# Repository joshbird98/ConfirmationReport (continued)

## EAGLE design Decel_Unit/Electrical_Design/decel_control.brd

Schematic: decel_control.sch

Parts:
ADC_FAST_HV1_FB: MCP33131; MSOP10
ADC_HV1_ELECTRODE_CURRENT, ADC_HV1_FG: MCP33131; MSOP10
ADC_SLOW_HV1_FB: MAX11270; TSSOP24
ADC_TEMP_DAC_HV1_CTRL: MCP33131; MSOP10
BNC_DECEL_COPY: BNC_RS
C1, C2, C4, C9, C10, C11, C13, C15, C16, C17, C18, C23, C24, C28, C34, C35, C36, C38, C45, C55, C56, C58, C59, C60, C64, C68, C74, C76, C79, C84, C89, C90, C91, C92, C103, C104, C109, C122, C132, C135, C136: 100n; C0805
C3, C5, C51: 10u; SMC_B
C6, C7, C8, C19, C20, C21, C30, C31, C32, C61, C62, C63, C66, C70, C110, C129, C130: 10u; C/6032-28R
C12, C14, C37, C54, C65, C77, C98, C133, C137: 1n; C0805
C22, C67, C72, C73, C80, C83, C93, C94, C95, C96, C97, C124, C126: 10n; C0805
C25, C57, C69, C75, C99, C105, C106, C113, C115, C125, C127, C131, C134: 1u; C0805
C26, C71, C78, C123: 1.7n; C0805
C27, C33, C40, C46, C47, C53: 0.1uF; 0402-TIGHT
C29, C43: 2.2uF; 0402-TIGHT
C39, C41: 15pF; 0402-TIGHT
C42, C52, C82, C85, C86, C87, C88: 100u; D/7343-31W
C44, C50: 22pF; 0402-TIGHT
C48: 1.0uF; 0402-TIGHT
C49: 4.7uF; 0402-TIGHT
C81: 2n; C0805
C100, C101: 100n; C0603
C102, C118: 10u; C0603
C107, C108, C117, C121: 22u; C0603
C111, C112: 1n; C0603
C114, C120: 2u2; C0603
C116, C128: 10n_C0G; C0805
C119: 10n; C0603
CLIP1, CLIP2, CLIP3, CLIP4: RFI_SHIELD_CLIP
CONN1: PSU_CONNECTOR; PSU_CONNECTION
D1, D2, D3, D4, D5, D6: BAS40-04; SOT23
DAC_HV1_CTRL: AD5763; TQFP-32
DAC_ULTRAVOLT_CTRL: AD5763; TQFP-32
EXT_INTERLOCK: KK-156-2
FRONT_PANEL_INTERLOCK: KK-156-2
F_RX1: HFBR-2412-TZ; HFBR-X41XZ
F_TX1: HFBR-1412-TZ; HFBR-X41XZ
HV_ENABLED_LED: LEDCHIPLED_0805; CHIPLED_0805
HV_PSU1, HV_PSU2: ULTRAVOLT_20A
IC1, IC2, IC3, IC4, IC5, IC6, IC9, IC10: ADA4522-4; SO14
IC7, IC8: AD8034; SOIC8
IP_BNC_HV1_FB, IP_BNC_HV1_PSU_EXTERNAL_OFFSET: BNC_RS
J1: MTA04-156; 1X4MTA
JP1: PINHD-1X8-3.5MM; 1X08-3.5MM
K1, K3: FINDER-30.22
K2: AQY41SOP; SOP04
LED1, LED2, LED3: LEDCHIP-LED0805; CHIP-LED0805
LID1_INTERLOCK, LID2_INTERLOCK: KK-156-2
MUX1: TMUX1104; VSSOP-10
OP_BNC_HV1_FG_COPY: BNC_RS
Q1: MOSFET-NREFLOW; SOT23
R1, R27, R28, R51, R54, R55, R61, R69, R108, R109, R110, R111, R112: 1k; R0805
R2: 88; R0805
R3, R102: 560; R0805
R4, R5, R6, R11, R12, R21, R22, R23, R25, R39, R41, R43, R49, R50, R56, R57, R58, R60, R63, R64, R65, R67, R68, R70, R71, R73, R78, R85, R86, R87, R91: 1000; R0805
R7, R10, R24, R31, R32, R34, R35, R36, R37, R52, R93, R98, R105, R107: 10k; R0805
R8, R62, R100: 100; R0805
R9: 200; R0805
R13, R18: 11k; R0805
R14, R15, R16, R17, R19, R20: 18k; R0805
R26, R53, R59, R106: 22; R0805
R29, R30: 22; 0402-TIGHT
R33, R38, R44, R46, R81, R82, R83, R84: 10; R0805
R40: 7500; R0805
R42: 5.1k; 0402-TIGHT
R45: 20000; R0805
R47: 15000; R0805
R48: 68000; R0805
R66: dnf; R0805
R72: 390; R0805
R74: 20k; R0805
R75: 330; R0805
R76, R116: 100k; R0805
R77: 270; R0805
R79: 1800; R0805
R80: 430; R0805
R88, R89: 1300; R0805
R90, R92: 150.0; R0805
R94, R96, R97, R99, R101, R103, R104: 7k32; R0603
R95: 5k11; R0603
R113: 82k; R0805
R114: 1000k; R0805
R115: 22k; R0805
TC1: MAX31855; SOIC8
TMP1, TMP2: MCP9700; SC70-5L
TP_REF, TP_REF1: TPB1,27; B1,27
TRIM1, TRIM2: 20; BOURNS_TRIMPOT
TRIM3: 10k; BOURNS_TRIMPOT
U1: STM32F405RGT6; TQFP64
U$1: SN75451; SOIC8
U$2: POWER_BOARD_DECEL
VREF1: MAX6225ACSA+; SOIC8
VREG1: LT3085; MSOP8
X1: PN61729-S
X2: 22-23-2021
X3: 2510-; PAK100/2500-10
X4: W237-102
Y1: 32.768kHz; CRYSTAL-SMD-3.2X1.5MM
Y2: 12MHz; CRYSTAL-SMD-5X3.2-4PAD

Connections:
0: ADC_FAST_HV1_FB.4 (AIN-), ADC_FAST_HV1_FB.5 (GND), ADC_HV1_ELECTRODE_CURRENT.4 (AIN-), ADC_HV1_ELECTRODE_CURRENT.5 (GND), ADC_HV1_FG.4 (AIN-), ADC_HV1_FG.5 (GND), ADC_SLOW_HV1_FB.10 (AVSS), ADC_SLOW_HV1_FB.11 (AINN), ADC_SLOW_HV1_FB.13 (REFN), ADC_SLOW_HV1_FB.17 (AVSS2), ADC_TEMP_DAC_HV1_CTRL.4 (AIN-), ADC_TEMP_DAC_HV1_CTRL.5 (GND), BNC_DECEL_COPY.P$1 (S4), BNC_DECEL_COPY.P$2 (S3), BNC_DECEL_COPY.P$3 (S2), BNC_DECEL_COPY.P$4 (S1), C6.+, C7.-, C9.2, C11.2, C12.2, C13.1, C14.1, C15.2, C16.2, C17.2, C18.2, C19.+, C20.-, C21.-, C22.2, C24.2, C25.2, C26.2, C28.2, C30.+, C31.-, C34.2, C35.2, C37.2, C38.2, C54.1, C55.1, C57.2, C58.2, C59.2, C60.2, C61.-, C62.-, C63.+, C64.1, C65.1, C66.-, C67.2, C69.2, C70.-, C71.2, C72.2, C73.1, C75.2, C76.2, C77.2, C78.2, C79.2, C80.2, C81.2, C83.1, C85.-, C86.-, C87.-, C90.2, C91.2, C92.2, C93.2, C94.2, C95.2, C96.2, C97.2, C98.2, C99.2, C100.2, C101.2, C102.1, C103.2, C104.2, C105.2, C106.2, C109.2, C110.-, C111.2, C112.2, C113.2, C114.2, C115.2, C116.1, C118.2, C119.2, C120.2, C123.2, C124.1, C126.2, C127.2, C129.-, C130.-, C131.2, C132.1, C133.1, C134.2, C135.2, C136.2, C137.2, CLIP1.P$1, CLIP1.P$2, CLIP1.P$3, CLIP2.P$1, CLIP2.P$2, CLIP2.P$3, CLIP3.P$1, CLIP3.P$2, CLIP3.P$3, CLIP4.P$1, CLIP4.P$2, CLIP4.P$3, D2.1 (A1), D3.1 (A1), D4.1 (A1), D5.1 (A1), D6.1 (A1), DAC_HV1_CTRL.P$14 (PGND), DAC_HV1_CTRL.P$20 (AGNDB), DAC_HV1_CTRL.P$21 (AGNDA), DAC_HV1_CTRL.P$28 (REFGND), DAC_ULTRAVOLT_CTRL.P$14 (PGND), DAC_ULTRAVOLT_CTRL.P$20 (AGNDB), DAC_ULTRAVOLT_CTRL.P$21 (AGNDA), DAC_ULTRAVOLT_CTRL.P$28 (REFGND), HV_ENABLED_LED.C, HV_PSU1.J1-5 (J1-5_SGND), HV_PSU2.J1-5 (J1-5_SGND), IC1.3 (+IN), IC1.5 (+IN), IC1.10 (+IN), IC1.12 (+IN), IC2.3 (+IN), IC2.5 (+IN), IC2.10 (+IN), IC3.3 (+IN), IC3.5 (+IN), IC4.10 (+IN), IC5.3 (+IN), IC5.10 (+IN), IC6.12 (+IN), IC9.2 (-IN), IC9.6 (-IN), IC9.9 (-IN), IC9.13 (-IN), IC10.10 (+IN), IP_BNC_HV1_FB.P$1 (S4), IP_BNC_HV1_FB.P$2 (S3), IP_BNC_HV1_FB.P$3 (S2), IP_BNC_HV1_FB.P$4 (S1), IP_BNC_HV1_PSU_EXTERNAL_OFFSET.P$1 (S4), IP_BNC_HV1_PSU_EXTERNAL_OFFSET.P$2 (S3), IP_BNC_HV1_PSU_EXTERNAL_OFFSET.P$3 (S2), IP_BNC_HV1_PSU_EXTERNAL_OFFSET.P$4 (S1), K2.2 (K), MUX1.P$3 (GND), OP_BNC_HV1_FG_COPY.P$1 (S4), OP_BNC_HV1_FG_COPY.P$2 (S3), OP_BNC_HV1_FG_COPY.P$3 (S2), OP_BNC_HV1_FG_COPY.P$4 (S1), Q1.2 (S), R23.2, R24.2, R48.1, R51.1, R68.1, R87.1, R98.1, R107.2, R114.1, R115.1, TC1.1 (GND), TMP1.2 (GND), TMP2.2 (GND), TRIM1.P$1 (A), TRIM1.P$2 (S), TRIM3.P$3 (E), U$2.P$15 (3), U$2.P$16 (4), U$2.P$18 (6), VREF1.4 (GND)
!RESET: C53.1, R42.1, U1.7 (NRST), X3.10
+2.048V: C18.1, C60.1, C62.+, DAC_HV1_CTRL.P$25 (REFA), DAC_HV1_CTRL.P$26 (REFB), DAC_ULTRAVOLT_CTRL.P$25 (REFA), DAC_ULTRAVOLT_CTRL.P$26 (REFB), IC3.13 (-IN), IC3.14 (OUT), R15.2, R16.2, R19.2, R20.2, R43.1
+3V3_CLEAN: C87.+, C92.1, C109.1, R83.2, TMP2.4 (VDD)
+12V: C80.1, C93.1, C95.1, C96.1, C104.1, C106.1, C136.1, C137.1, IC5.4 (VCC), IC6.4 (VCC), IC7.8 (VCC), IC8.8 (VCC), IC10.4 (VCC), R82.1, U$2.P$29 (5), U$2.P$30 (6), VREG1.5 (VCTRL), VREG1.7 (IN), VREG1.8 (IN)
+12V_CLEAN: C86.+, C91.1, C101.1, C112.1, C119.1, C120.1, IC9.4 (VCC), R82.2, VREF1.2 (VIN)
+24V: C12.1, C15.1, C28.1, C34.1, C37.1, C76.1, C77.1, IC1.4 (VCC), IC2.4 (VCC), IC3.4 (VCC), IC4.4 (VCC), U$2.P$33 (9), U$2.P$34 (10)
+24V_FG: K3.24 (S), K3.A1 (1), U$2.P$4 (4), U$2.P$5 (5), U$2.P$6 (6)
+24V_ULTRAVOLT_A: K1.14 (S), K1.A1 (1), U$2.P$9 (9), U$2.P$10 (10)
+24V_ULTRAVOLT_B: K1.24 (S), U$2.P$11 (11), U$2.P$12 (12)
+A1V8: ADC_FAST_HV1_FB.2 (AVDD), ADC_HV1_ELECTRODE_CURRENT.2 (AVDD), ADC_HV1_FG.2 (AVDD), ADC_TEMP_DAC_HV1_CTRL.2 (AVDD), C25.1, C69.1, C75.1, C127.1, U$2.P$13 (1)
+A3V3: ADC_SLOW_HV1_FB.9 (AVDD), C115.1, C135.1, R83.1, R100.2, TC1.4 (VCC), U$2.P$25 (1), U$2.P$26 (2)
+A5V: C2.1, C3.+, C4.1, C5.+, C7.+, C9.1, C16.1, C20.+, C31.+, C35.1, C59.1, C61.+, C79.1, DAC_HV1_CTRL.P$13 (AVDD1), DAC_HV1_CTRL.P$31 (AVDD2), DAC_ULTRAVOLT_CTRL.P$13 (AVDD1), DAC_ULTRAVOLT_CTRL.P$31 (AVDD2), MUX1.P$5 (EN), MUX1.P$6 (VCC), R1.1, R2.2, U$1.8 (VCC), U$2.P$17 (5)
+D3V3: ADC_FAST_HV1_FB.9 (SDI), ADC_FAST_HV1_FB.10 (DVIO), ADC_HV1_ELECTRODE_CURRENT.9 (SDI), ADC_HV1_ELECTRODE_CURRENT.10 (DVIO), ADC_HV1_FG.9 (SDI), ADC_HV1_FG.10 (DVIO), ADC_SLOW_HV1_FB.22 (DVDD), ADC_TEMP_DAC_HV1_CTRL.9 (SDI), ADC_TEMP_DAC_HV1_CTRL.10 (DVIO), C1.1, C8.+, C10.1, C23.1, C27.1, C32.+, C33.1, C36.1, C40.1, C47.1, C68.1, C74.1, C122.1, C125.1, DAC_HV1_CTRL.P$12 (DVCC), DAC_HV1_CTRL.P$32 (BIN_2CMP), DAC_ULTRAVOLT_CTRL.P$12 (DVCC), DAC_ULTRAVOLT_CTRL.P$32 (BIN_2CMP), F_RX1.P$2, JP1.5, JP1.6, R3.1, R10.1, R32.1, R42.2, R44.1, R105.2, U1.19 (VDD1), U1.32 (VDD2), U1.42 (PA9/UART1_TX), U1.43 (PA10/UART1_RX), U1.48 (VDD3), U1.64 (VDD4), U$2.P$35 (11), U$2.P$36 (12), X2.1, X3.3, X3.4
+D3V3_CLEAN: C46.1, C48.1, C49.1, C51.+, R44.2, U1.13 (VDDA)
-12V: C13.2, C14.2, C24.1, C54.2, C55.2, C64.2, C65.2, C73.2, C83.2, C94.1, C97.1, C132.2, C133.2, IC1.11 (GND), IC2.11 (GND), IC3.11 (GND), IC4.11 (GND), IC5.11 (GND), IC6.11 (GND), IC7.4 (GND), IC8.4 (GND), IC10.11 (GND), R81.1, U$2.P$27 (3), U$2.P$28 (4)
-12V_CLEAN: C85.+, C90.1, C100.1, C111.1, IC9.11 (GND), R81.2
-A5V: C6.-, C11.1, C17.1, C19.-, C30.-, C38.1, C58.1, C63.-, DAC_HV1_CTRL.P$15 (AVSS1), DAC_HV1_CTRL.P$30 (AVSS2), DAC_ULTRAVOLT_CTRL.P$15 (AVSS1), DAC_ULTRAVOLT_CTRL.P$30 (AVSS2), U$2.P$14 (2)
BOOT0: R116.2, U1.60 (BOOT0), X2.2
CS_ADC_FAST_HV1_FB: ADC_FAST_HV1_FB.6 (CNVST), U1.37 (PC6/I2S2_MCK)
CS_ADC_HV1_ELECTRODE_CURRENT: ADC_HV1_ELECTRODE_CURRENT.6 (CNVST), U1.17 (PA3/UART2_RX)
CS_ADC_HV1_FG: ADC_HV1_FG.6 (CNVST), U1.22 (PA6/SPI1_MISO)
CS_ADC_SLOW_HV1_FB: ADC_SLOW_HV1_FB.23 (CSB), U1.33 (PB12/I2S2_WS)
CS_ADC_TEMP_DAC_HV1_CTRL: ADC_TEMP_DAC_HV1_CTRL.6 (CNVST), U1.54 (PD2/SDIO_CMD)
CS_DISPLAY: JP1.4, U1.26 (PB0)
CS_TC_RES_STACK: TC1.6 (!CS), U1.38 (PC7)
GAIN_A: MUX1.P$10 (A1), U1.21 (PA5/SPI1_SCK)
GAIN_B: MUX1.P$1 (A0), U1.20 (PA4/SPI1_NSS)
GND: ADC_SLOW_HV1_FB.3 (DGND), ADC_SLOW_HV1_FB.4 (SYNC), ADC_SLOW_HV1_FB.20 (DGND), C1.2, C2.2, C3.-, C4.2, C5.-, C8.-, C10.2, C23.2, C27.2, C29.2, C32.-, C33.2, C36.2, C39.2, C40.2, C41.2, C43.2, C44.2, C46.2, C47.2, C48.2, C49.2, C50.2, C51.-, C53.2, C68.2, C74.2, C122.2, C125.2, DAC_HV1_CTRL.P$5 (!CLR), DAC_HV1_CTRL.P$6 (!LDAC), DAC_HV1_CTRL.P$11 (DGND), DAC_ULTRAVOLT_CTRL.P$5 (!CLR), DAC_ULTRAVOLT_CTRL.P$6 (!LDAC), DAC_ULTRAVOLT_CTRL.P$11 (DGND), F_RX1.P$3, F_RX1.P$7, F_TX1.P$1, F_TX1.P$3 (CATHODE), F_TX1.P$4, F_TX1.P$5, F_TX1.P$8, JP1.7, JP1.8, LED1.C, LED2.C, LED3.C, R7.1, R116.1, U1.12 (VSSA), U1.18 (VSS1), U1.28 (PB2-BOOT1), U1.63 (VSS2), U$1.4 (GND), U$2.P$19 (7), U$2.P$20 (8), U$2.P$21 (9), U$2.P$22 (10), U$2.P$23 (11), U$2.P$24 (12), U$2.P$31 (7), U$2.P$32 (8), X1.4, X1.S1, X1.S2, X3.7, X3.8
HV1_COARSE_CTRL: IC3.8 (OUT), R37.1, R45.1
HV1_CTRL: C88.+, C89.1, CONN1.P$7, CONN1.P$17, R84.2
HV1_CURRENT_MON: IC4.3 (+IN), IC6.8 (OUT), R75.1, R78.1, R80.1
HV1_FB: IC10.3 (+IN), IP_BNC_HV1_FB.P$5 (S)
HV1_FB_BUFF: IC4.12 (+IN), IC10.1 (OUT), IC10.2 (-IN), IC10.5 (+IN), R109.2, R112.1
HV1_FB_LPF: IC10.13 (-IN), IC10.14 (OUT), R111.1
HV1_FG: CONN1.P$9, CONN1.P$10, CONN1.P$19, CONN1.P$20, IC8.3 (+IN), IC8.6 (-IN), K2.3 (DS2), R93.2, U$2.P$1 (1), U$2.P$2 (2), U$2.P$3 (3)
HV1_FG_UNBUFF: C42.-, C45.2, C52.-, C56.2, C82.-, C84.2, C88.-, C89.2, IC5.8 (OUT), IC7.5 (+IN), IC8.5 (+IN), R34.1, R52.2, R57.2
HV1_FINE_CTRL: DAC_HV1_CTRL.P$19 (VOUTB), R70.2, R71.2
HV_ENABLE: FRONT_PANEL_INTERLOCK.2, HV_PSU1.J1-4 (J1-4_EN), HV_PSU2.J1-4 (J1-4_EN), Q1.1 (G), R7.2, R8.1, R9.2, R24.1, R102.1
HV_ENABLE_RETURN: D1.2 (C2), U1.50 (PA15/JTDI)
HV_ENABLE_SOFTWARE: EXT_INTERLOCK.1, U1.52 (PC11/SDIO_D3)
LED_1: R6.1, U1.39 (PC8/SDIO_D0)
LED_2: R5.1, U1.40 (PC9/SDIO_D1)
LED_3: R4.1, U1.41 (PA8)
unnamed: IC9.8 (OUT), R96.1, R97.2, R101.1
unnamed: C114.1, VREF1.3 (NR)
unnamed: IC9.12 (+IN), R101.2, R103.1
unnamed: C118.1, R104.1, TRIM3.P$1 (A), VREF1.6 (OUT)
unnamed: IC10.8 (OUT), IC10.9 (-IN)
unnamed: DAC_ULTRAVOLT_CTRL.P$22 (VOUTA), R17.2
unnamed: K1.A2 (2), Q1.3 (D)
unnamed: CONN1.P$5, CONN1.P$15, K3.11
unnamed: C117.1, C121.1, IC9.3 (+IN), R96.2, R104.2
unnamed: C117.2, C121.2, IC9.1 (OUT), R99.1
unnamed: IC4.2 (-IN), R56.1, R58.2, R62.2, R63.2, R64.2
unnamed: C107.1, C108.1, IC9.5 (+IN), R95.1, R99.2
unnamed: IC9.10 (+IN), R94.2, R97.1
unnamed: C102.2, C107.2, C108.2, IC9.7 (OUT), R94.1, R95.2
unnamed: IC1.6 (-IN), R13.2, R14.1, R15.1, R16.1
unnamed: D5.3 (C1A2), R106.2, R108.1
unnamed: ADC_FAST_HV1_FB.3 (AIN+), C123.1, R106.1
unnamed: R108.2, R109.1
unnamed: EXT_INTERLOCK.2, LID1_INTERLOCK.1
unnamed: LID1_INTERLOCK.2, LID2_INTERLOCK.1
unnamed: FRONT_PANEL_INTERLOCK.1, LID2_INTERLOCK.2
unnamed: D1.1 (A1), D1.3 (C1A2), R8.2
unnamed: C134.1, IC10.12 (+IN), R112.2
unnamed: CONN1.P$6, CONN1.P$16, K3.14 (S)
unnamed: IC1.2 (-IN), R17.1, R18.2, R19.1, R20.1
unnamed: IC2.13 (-IN), R23.1, R25.2
unnamed: IC1.1 (OUT), R18.1, R22.2
unnamed: IC1.7 (OUT), R12.2, R13.1
unnamed: ADC_SLOW_HV1_FB.12 (AINP), C116.2, D6.3 (C1A2), R110.2
unnamed: IC1.9 (-IN), R11.2, R12.1
unnamed: ADC_SLOW_HV1_FB.19 (CLK), R107.1
unnamed: ADC_SLOW_HV1_FB.16 (CAPP), C128.2
unnamed: ADC_SLOW_HV1_FB.15 (CAPN), C128.1
unnamed: ADC_SLOW_HV1_FB.21 (CAPREG), C131.1
unnamed: IC6.2 (-IN), R90.1, R91.2
unnamed: K2.4 (DS1), K3.A2 (2)
unnamed: HV_ENABLED_LED.A, R9.1
unnamed: IC1.13 (-IN), R21.2, R22.1
unnamed: DAC_ULTRAVOLT_CTRL.P$19 (VOUTB), R14.2
unnamed: CONN1.P$2, CONN1.P$12, K3.21
unnamed: HV_PSU1.J1-2 (J1-2_VIN), HV_PSU1.J1-9 (J1-9_VIN), K1.21
unnamed: K2.1 (A), R102.2
unnamed: HV_PSU2.J1-2 (J1-2_VIN), HV_PSU2.J1-9 (J1-9_VIN), K1.11
unnamed: R88.1, R90.2
unnamed: IC6.6 (-IN), R91.1, R92.2
unnamed: R89.2, R92.1
unnamed: IC6.7 (OUT), R86.2, R89.1
unnamed: IC6.1 (OUT), R85.2, R88.2
unnamed: IC6.10 (+IN), R86.1, R87.2
unnamed: IC6.9 (-IN), R78.2, R85.1
unnamed: IC7.6 (-IN), IC7.7 (OUT), OP_BNC_HV1_FG_COPY.P$5 (S)
unnamed: TRIM3.P$2 (S), VREF1.5 (TRIM)
unnamed: IC10.6 (-IN), R113.1, R114.2, R115.2
unnamed: IC6.5 (+IN), IC7.1 (OUT), IC7.2 (-IN)
unnamed: IC6.3 (+IN), IC8.1 (OUT), IC8.2 (-IN)
unnamed: C39.1, U1.3 (PC14), Y1.P$2 (2)
unnamed: C113.1, R100.1, TMP1.4 (VDD)
unnamed: IC7.3 (+IN), IC8.7 (OUT), R93.1
unnamed: MUX1.P$2 (S1), R63.1
unnamed: IC4.1 (OUT), R56.2, R65.2
unnamed: IC4.14 (OUT), R49.2, R50.1
unnamed: IC4.5 (+IN), R49.1, R68.2
unnamed: IC4.6 (-IN), R60.2, R65.1
unnamed: D3.3 (C1A2), R53.2, R55.1
unnamed: ADC_HV1_ELECTRODE_CURRENT.3 (AIN+), C71.1, R53.1
unnamed: IC4.7 (OUT), R54.2, R60.1
unnamed: MUX1.P$9 (S2), R58.1
unnamed: C41.1, U1.4 (PC15), Y1.P$1 (1)
unnamed: C50.1, U1.6 (PH1), Y2.3 (2)
unnamed: C44.1, U1.5 (PH0), Y2.1
unnamed: C29.1, U1.47 (VCAP2)
unnamed: MUX1.P$4 (S3), R64.1
unnamed: C43.1, U1.31 (VCAP1)
unnamed: LED3.A, R6.2
unnamed: MUX1.P$7 (S4), R62.1
unnamed: R30.2, U1.44 (PA11)
unnamed: IC4.13 (-IN), MUX1.P$8 (D1), R50.2
unnamed: R29.2, U1.45 (PA12)
unnamed: R1.2, U$1.1 (1A)
unnamed: IC4.8 (OUT), IC4.9 (-IN)
unnamed: F_TX1.P$2 (ANODE), F_TX1.P$6 (ANODE), F_TX1.P$7 (ANODE), R2.1, U$1.3 (1Y)
unnamed: LED2.A, R5.2
unnamed: LED1.A, R4.2
unnamed: IC2.1 (OUT), IC2.2 (-IN)
unnamed: IC2.6 (-IN), IC2.7 (OUT)
unnamed: IC2.8 (OUT), IC2.9 (-IN)
unnamed: IC6.13 (-IN), R77.2, R79.1
unnamed: R77.1, R80.2
unnamed: IC6.14 (OUT), R76.1, R79.2
unnamed: C81.1, IC5.5 (+IN), R76.2
unnamed: IC5.6 (-IN), IC5.7 (OUT), R73.1
unnamed: R74.1, R75.2
unnamed: IC5.2 (-IN), R72.1, R74.2
unnamed: IC5.1 (OUT), R67.1, R72.2
unnamed: DAC_HV1_CTRL.P$22 (VOUTA), R39.2
unnamed: IC3.2 (-IN), R34.2, R35.1, R37.2
unnamed: IC3.12 (+IN), R47.1, R48.2
unnamed: ADC_TEMP_DAC_HV1_CTRL.3 (AIN+), C26.1, R26.1
unnamed: DAC_HV1_CTRL.P$29 (TEMP), R28.2
unnamed: C57.1, IC3.10 (+IN), R41.1, R43.2
unnamed: R39.1, R41.2
unnamed: IC3.9 (-IN), R40.1, R45.2
unnamed: IC5.9 (-IN), R57.1, R66.1, R67.2, R70.1, R71.1, R73.2
unnamed: R110.1, R111.2
unnamed: IC3.6 (-IN), R31.2, R36.1
unnamed: IC3.1 (OUT), R31.1, R35.2
unnamed: IC3.7 (OUT), R33.1, R36.2
unnamed: C52.+, C56.1, R38.2, R46.1
unnamed: C42.+, C45.1, R33.2, R38.1
unnamed: C82.+, C84.1, R46.2, R84.1
unnamed: IP_BNC_HV1_PSU_EXTERNAL_OFFSET.P$5 (S), R66.2
unnamed: IC5.13 (-IN), IC5.14 (OUT), R69.2
unnamed: IC5.12 (+IN), R51.2, R52.1
unnamed: R54.1, R55.2
unnamed: D2.3 (C1A2), R26.2, R27.1
unnamed: R27.2, R28.1
unnamed: BNC_DECEL_COPY.P$5 (S), IC10.7 (OUT), R113.2
unnamed: R40.2, TRIM1.P$3 (E)
unnamed: R47.2, TRIM2.P$1 (A), TRIM2.P$2 (S)
unnamed: D4.3 (C1A2), R59.2, R61.1
unnamed: ADC_HV1_FG.3 (AIN+), C78.1, R59.1
unnamed: R61.2, R69.1
RDY_ADC_SLOW_HV1_FB: ADC_SLOW_HV1_FB.18 (RDYB), U1.23 (PA7/SPI1_MOSI)
RST_ADC_SLOW_HV1_FB: ADC_SLOW_HV1_FB.5 (RSTB), R105.1
RST_DAC_HV1_CTRL: DAC_HV1_CTRL.P$10 (!RSTIN), R32.2
RST_DAC_ULTRAVOLT_CTRL: DAC_ULTRAVOLT_CTRL.P$10 (!RSTIN), R10.2
SPI0_MISO: ADC_FAST_HV1_FB.7 (SDO), ADC_HV1_ELECTRODE_CURRENT.7 (SDO), ADC_HV1_FG.7 (SDO), ADC_SLOW_HV1_FB.2 (DOUT), JP1.1, TC1.7 (SO), U1.35 (PB14/I2S2_XD)
SPI0_MOSI: ADC_SLOW_HV1_FB.1 (DIN), JP1.3, U1.36 (PB15/I2S2_SD)
SPI0_SCLK: ADC_FAST_HV1_FB.8 (SCLK), ADC_HV1_ELECTRODE_CURRENT.8 (SCLK), ADC_HV1_FG.8 (SCLK), ADC_SLOW_HV1_FB.24 (SCLK), JP1.2, TC1.5 (SCK), U1.34 (PB13/I2S2_CK)
SPI1_MISO: ADC_TEMP_DAC_HV1_CTRL.7 (SDO), DAC_HV1_CTRL.P$4 (SDO), DAC_ULTRAVOLT_CTRL.P$4 (SDO), U1.56 (PB4/JTRST)
SPI1_MOSI: DAC_HV1_CTRL.P$3 (SDIN), DAC_ULTRAVOLT_CTRL.P$3 (SDIN), U1.57 (PB5)
SPI1_SCLK: ADC_TEMP_DAC_HV1_CTRL.8 (SCLK), DAC_HV1_CTRL.P$2 (SCLK), DAC_ULTRAVOLT_CTRL.P$2 (SCLK), U1.55 (PB3/JTDO)
SWCLK: U1.49 (PA14/JTCK), X3.5
SWDIO: U1.46 (PA13/JTMS), X3.9
SYNC_DAC_HV1_CTRL: DAC_HV1_CTRL.P$1 (!SYNC), U1.58 (PB6)
SYNC_DAC_ULTRAVOLT_CTRL: DAC_ULTRAVOLT_CTRL.P$1 (!SYNC), U1.53 (PC12/SDIO_CLK)
T+: TC1.3 (T+), X4.1
T-: TC1.2 (T-), X4.2
TEMP_MON_ADC_FB: TMP1.3 (VOUT), U1.24 (PC4)
TEMP_MON_VREF: TMP2.3 (VOUT), U1.25 (PC5)
UART_RX: F_RX1.P$6, R3.2, U1.30 (PB11)
UART_TX: U1.29 (PB10), U$1.2 (1B)
ULTRAVOLT_GND: HV_PSU1.J1-1 (J1-1_GND), HV_PSU1.J1-8 (J1-8_GND), HV_PSU2.J1-1 (J1-1_GND), HV_PSU2.J1-8 (J1-8_GND), U$2.P$7 (7), U$2.P$8 (8)
USB_D+: R29.1, X1.3
USB_D-: R30.1, X1.2
VPROG_ULTRAVOLT_A: HV_PSU2.J1-6 (J1-6_VPROG), IC1.14 (OUT), R21.1
VPROG_ULTRAVOLT_B: HV_PSU1.J1-6 (J1-6_VPROG), IC1.8 (OUT), R11.1
VREF: ADC_FAST_HV1_FB.1 (VREF), ADC_HV1_ELECTRODE_CURRENT.1 (VREF), ADC_HV1_FG.1 (VREF), ADC_SLOW_HV1_FB.14 (REFP), ADC_TEMP_DAC_HV1_CTRL.1 (VREF), C21.+, C22.1, C66.+, C67.1, C70.+, C72.1, C98.1, C99.1, C124.2, C126.1, C129.+, C130.+, IC2.12 (+IN), IC9.14 (OUT), R103.2, TP_REF.TP, TP_REF1.TP, TRIM2.P$3 (E), VREG1.4 (SET)
VREF_5V: HV_PSU1.J1-7 (J1-7_VREF), HV_PSU1.J1-13 (J1-13_IPROG), HV_PSU2.J1-7 (J1-7_VREF), HV_PSU2.J1-13 (J1-13_IPROG), IC2.14 (OUT), R25.1
VREF_TOUGH_BUFF: C103.1, C105.1, C110.+, D2.2 (C2), D3.2 (C2), D4.2 (C2), D5.2 (C2), D6.2 (C2), R98.2, VREG1.1 (OUT), VREG1.2 (OUT), VREG1.3 (OUT), VREG1.BOTTOM (OUT)
VUSB: X1.1

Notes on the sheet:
TACL225M016XTA
CPF0603B7K32E1
RT0603BRD075K11L
High stability voltage reference
Low pass filter 0.5Hz to reduce noise (including 0.1-10Hz)
Metal EMI shield to reduce noise and spread thermal fluctuations
Also use plastic enclosure to prevent temperature convection flows across the circuit. This means temperature across the circuit is uniform and slow-changing, making it easier to compensate.
Voltage Reference
Unity Gain Buffer
First order LPF, 16Hz For removing noise and anti-aliasing
Monitors DC component of lens voltage at very low sample rate
JFET buffers need guard rings
Differential, gain 3.9
Gain = - 2.571
Gain = - 1/52.13
RC filter, matching HV filter
Sum RC-filtered and non-filtered signals
This signal matches the error induced by the beam current striking the decel lens and high voltage RC filter It is summed with the "fine HV control" offset signal (-8.192V to +8.192V)
DAC temperature reading
HV1 Coarse Control Signal GND referenced, 0-10V
-4096V to +4.096V
Fine HV Control (HP020 offset)
Sums the 0-10V control signal with the HV1 floating ground offset, so that it is referenced appropriately.
This analogue voltage can provide fine tuning of the HV PSU Floating Offset so that the lens voltage can be controlled to higher resolution than with the coarse control alone.
Low-Pass filter for the HV1 control signal
Temperature monitor to enable software compensation of temperature drift
Decel Voltage (0-10V for 0-20kV)
Gain = 4.809
Add some extra signal, so that the accel source can add some fast transients if needed to counteract source fluctuations
These op-amps should be +26V -12V
3V3 UART Tx Signal In
3V3 UART Rx Signal Out
5Mbps Fibre Optic Link
HV1 Control Signal Synthesiser - Dual High Precision DAC
HV1 Feedback Digitiser and Analog Monitor Outputs
Digital Interface and Daughter Connections
Tune to get accurate 0-10V from opamp output
HV1 Beam Compensation, Floating Ground (FG) Synthesis
S02-20150300
Electrode Current Digitiser HV1 Power Supply Current - Feedback Resistor Stack Current = Electrode Current Sampled at 1Msps and results integrated and stored digitally

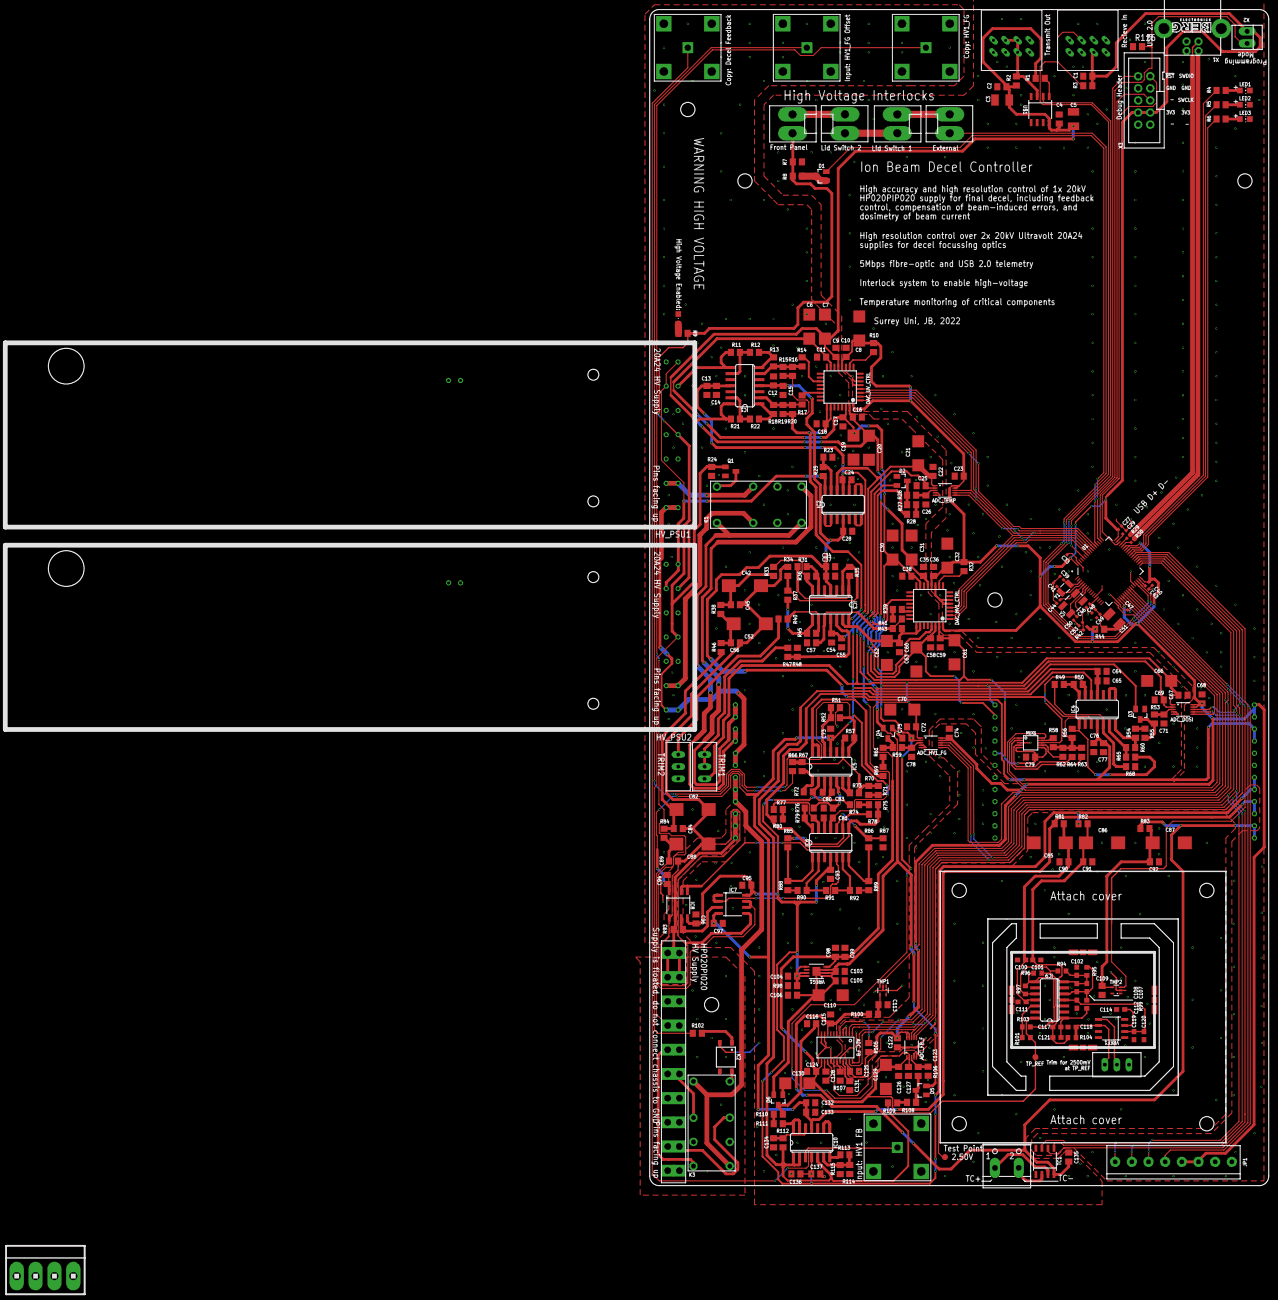
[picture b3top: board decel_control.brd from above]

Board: 2 copper layers, 130.0 x 247.0 mm, 323 parts (0 on the bottom side), 194 nets.

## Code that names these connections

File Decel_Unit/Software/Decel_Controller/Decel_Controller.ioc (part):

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Mcu.Name=STM32F405RGTx
Mcu.Package=LQFP64
Mcu.UserName=STM32F405RGTx
PA11.Mode=Device_Only
PA11.Signal=USB_OTG_FS_DM
PA12.Mode=Device_Only
PA12.Signal=USB_OTG_FS_DP
PA13.Mode=Serial_Wire
PA13.Signal=SYS_JTMS-SWDIO
PA14.Mode=Serial_Wire
PA14.Signal=SYS_JTCK-SWCLK
PA15.GPIOParameters=GPIO_PuPd,GPIO_Label
PA15.GPIO_Label=HV_ENABLE_RETURN
PA15.GPIO_PuPd=GPIO_PULLDOWN
PA15.Signal=GPIO_Input
PA3.GPIOParameters=GPIO_Speed,PinState,GPIO_Label
PA3.GPIO_Label=CS_ADC_HV1_ELECTRODE_CURRENT
PA3.GPIO_Speed=GPIO_SPEED_FREQ_VERY_HIGH
PA3.PinState=GPIO_PIN_SET
PA3.Signal=GPIO_Output
PA4.GPIOParameters=GPIO_Label
PA4.GPIO_Label=GAIN_B
PA4.Signal=GPIO_Output
PA5.GPIOParameters=GPIO_Label
PA5.GPIO_Label=GAIN_A
PA5.Signal=GPIO_Output
PA6.GPIOParameters=GPIO_Speed,PinState,GPIO_Label
PA6.GPIO_Label=CS_ADC_HV1_FG
PA6.GPIO_Speed=GPIO_SPEED_FREQ_VERY_HIGH
PA6.PinState=GPIO_PIN_SET
PA6.Signal=GPIO_Output
PA7.GPIOParameters=GPIO_Label
PA7.GPIO_Label=RDY_ADC_SLOW_HV1_FB
PA7.Signal=GPIO_Input
PA8.GPIOParameters=GPIO_Label
PA8.GPIO_Label=LED_3
PA8.Signal=GPIO_Output
PB0.GPIOParameters=GPIO_Speed,PinState,GPIO_Label
PB0.GPIO_Label=CS_DISPLAY
PB0.GPIO_Speed=GPIO_SPEED_FREQ_VERY_HIGH
PB0.PinState=GPIO_PIN_SET
PB0.Signal=GPIO_Output
PB10.GPIOParameters=GPIO_Label
PB10.GPIO_Label=UART_TX
PB10.Mode=Asynchronous
PB10.Signal=USART3_TX
PB11.GPIOParameters=GPIO_Label
PB11.GPIO_Label=UART_RX
PB11.Mode=Asynchronous
PB11.Signal=USART3_RX
PB12.GPIOParameters=GPIO_Speed,PinState,GPIO_Label
PB12.GPIO_Label=CS_ADC_SLOW_HV1_FB
PB12.GPIO_Speed=GPIO_SPEED_FREQ_LOW
PB12.PinState=GPIO_PIN_SET
PB12.Signal=GPIO_Output
PB6.GPIOParameters=GPIO_Speed,PinState,GPIO_Label
PB6.GPIO_Label=SYNC_DAC_HV1_CTRL
PB6.GPIO_Speed=GPIO_SPEED_FREQ_VERY_HIGH
PB6.PinState=GPIO_PIN_SET
PB6.Signal=GPIO_Output
PC11.GPIOParameters=GPIO_Label
PC11.GPIO_Label=HV_ENABLE_SOFTWARE
PC11.Signal=GPIO_Output
PC12.GPIOParameters=GPIO_Speed,PinState,GPIO_Label
PC12.GPIO_Label=SYNC_DAC_ULTRAVOLT_CTRL
PC12.GPIO_Speed=GPIO_SPEED_FREQ_VERY_HIGH
PC12.PinState=GPIO_PIN_SET
PC12.Signal=GPIO_Output
PC14-OSC32_IN.Mode=LSE-External-Oscillator
PC14-OSC32_IN.Signal=RCC_OSC32_IN
PC15-OSC32_OUT.Mode=LSE-External-Oscillator
PC15-OSC32_OUT.Signal=RCC_OSC32_OUT
PC4.GPIOParameters=GPIO_Label
PC4.GPIO_Label=TEMP_MON_ADC_FB
PC4.Signal=ADCx_IN14
PC5.GPIOParameters=GPIO_Label
PC5.GPIO_Label=TEMP_MON_VREF
PC5.Signal=ADCx_IN15
PC6.GPIOParameters=GPIO_Speed,PinState,GPIO_Label
PC6.GPIO_Label=CS_ADC_FAST_HV1_FB
PC6.GPIO_Speed=GPIO_SPEED_FREQ_VERY_HIGH
PC6.PinState=GPIO_PIN_SET
PC6.Signal=GPIO_Output
PC7.GPIOParameters=GPIO_Speed,PinState,GPIO_Label
PC7.GPIO_Label=CS_TC_RES_STACK
PC7.GPIO_Speed=GPIO_SPEED_FREQ_VERY_HIGH
PC7.PinState=GPIO_PIN_SET
PC7.Signal=GPIO_Output
PC8.GPIOParameters=GPIO_Label
PC8.GPIO_Label=LED_1
PC8.Signal=GPIO_Output
PC9.GPIOParameters=GPIO_Label
PC9.GPIO_Label=LED_2
PC9.Signal=GPIO_Output
PD2.GPIOParameters=GPIO_Speed,PinState,GPIO_Label
PD2.GPIO_Label=CS_ADC_TEMP_DAC_HV1_CTRL
PD2.GPIO_Speed=GPIO_SPEED_FREQ_VERY_HIGH
PD2.PinState=GPIO_PIN_SET
PD2.Signal=GPIO_Output
PH0-OSC_IN.Mode=HSE-External-Oscillator
PH0-OSC_IN.Signal=RCC_OSC_IN
PH1-OSC_OUT.Mode=HSE-External-Oscillator
PH1-OSC_OUT.Signal=RCC_OSC_OUT
RCC.HSE_VALUE=12000000
RCC.SYSCLKFreq_VALUE=168000000
RCC.SYSCLKSource=RCC_SYSCLKSOURCE_PLLCLK
board=custom

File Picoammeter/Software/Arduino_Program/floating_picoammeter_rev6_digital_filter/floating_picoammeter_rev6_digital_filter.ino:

/*Floating Picoammeter rev 6 with digital filter Software
*/

// INCLUDES
#include <SPI.h>
#include <SoftwareSerial.h>
#include <IIRFilter.h>

// PIN DEFINES
#define ADC_CS A0
#define REED_RELAY_CONTROL A1
#define FIBRE_TRANSMIT A2
#define DEBUG_LED 4
#define SEL_RNG_1 8
#define SEL_RNG_2 7
#define SEL_RNG_3 10
#define SEL_RNG_4 9

// CONSTANTS

// GLOBAL VARIABLES, ARRAYS & OBJECTS
uint32_t adc_tally;
uint32_t adc_readings;
uint32_t large_tally;
uint16_t large_tally_length;
uint8_t range;
uint16_t last_adc_value;

uint8_t t1_flag;
uint32_t i;
long int lastTime;

unsigned long calibration_time; // time in millis() of most recent calibration
#define CALIBRATION_PERIOD 1000*60*2 //2 minutes
const double ADC_samplefreq  = 1600;  // this seems to actually end up as 1577.5 Hz

SoftwareSerial fibreOptic (A4, FIBRE_TRANSMIT, 1);

// FUNCTIONS

// sets the relays for the desired range, ensuring only one relay coil is driven
// includes small delay to ensure relay settles

void set_range(uint8_t rangeSelection)
{
  pinMode(REED_RELAY_CONTROL, OUTPUT);
  pinMode(SEL_RNG_1, OUTPUT);
  pinMode(SEL_RNG_2, OUTPUT);
  pinMode(SEL_RNG_3, OUTPUT);
  pinMode(SEL_RNG_4, OUTPUT);
  digitalWrite(REED_RELAY_CONTROL, LOW);
  digitalWrite(SEL_RNG_1, LOW);
  digitalWrite(SEL_RNG_2, LOW);
  digitalWrite(SEL_RNG_3, LOW);
  digitalWrite(SEL_RNG_4, LOW);
  if (rangeSelection > 0) digitalWrite(REED_RELAY_CONTROL, HIGH);
  if (rangeSelection == 1) digitalWrite(SEL_RNG_1, HIGH);
  if (rangeSelection == 2) digitalWrite(SEL_RNG_2, HIGH);
  if (rangeSelection == 3) digitalWrite(SEL_RNG_3, HIGH);
  
}

void reset_counter()
{
  adc_tally = 0;
  adc_readings = 0;
}

// interface with the MCP33131, returns a 16-bit measaurement
uint16_t read_adc()
{
  digitalWrite(ADC_CS, LOW);
  uint8_t msb = SPI.transfer(0xFF);
  uint8_t lsb = SPI.transfer(0xFF);
  digitalWrite(ADC_CS, HIGH);

  uint16_t value = (((uint16_t)msb << 8) | lsb);
  return value;
}

//interface with the MCP33131, performs recalibration if needed, takes up to 650ms
void calibrate_adc(uint8_t force_calibrate)
{
  //check if enough time has passed to need recalibration
  unsigned long now = millis();
  unsigned long elapsed = now - calibration_time;
  
  if ((elapsed > CALIBRATION_PERIOD) or (force_calibrate == 1))
  {
    digitalWrite(ADC_CS, LOW);
    for (uint8_t i = 0; i < 129; i++) //1024 clock cycles
    {
      SPI.transfer(0xFF);
    }
    delay(650); // max delay needed for t_cal
    digitalWrite(ADC_CS, HIGH);
    set_range(0);        // set relays and delay
    calibration_time = now;
  }
}

void flash_led()
{
  digitalWrite(DEBUG_LED, HIGH);
  delay(100);
  digitalWrite(DEBUG_LED, LOW);
}

void check_range(uint32_t value)
{
  //Serial.print("RANGE :");
  //Serial.println(range);
  //Serial.println(value);
  uint8_t new_range = range;
  if ((value < 4096) or (value > 61439))
  {
    if (range < 3) new_range += 1;  // range should be increased
  }
  // if ((value > 32550) and (value < 33005)) good for range 1 going into range 0
  if ((value > 32550) and (value < 33005))
  {
    if (range > 0) new_range -= 1;  // range should be decreased
  }
  if (new_range != range)
  {
    //Serial.print("OLD RANGE: ");
    //Serial.print(range);
    //Serial.print(" NEW RANGE: ");
    //Serial.println(new_range);
    range = new_range;
    set_range(range);
    adc_tally = 0;
    adc_readings = 0;
  }
}

void setup() {
  last_adc_value = 0;
  i = 0;
  lastTime = millis();
  t1_flag = 0;
  adc_tally = 0;
  adc_readings = 0;
  range = 0;
  pinMode(DEBUG_LED, OUTPUT);
  digitalWrite(DEBUG_LED, LOW);
  pinMode(ADC_CS, OUTPUT);
  pinMode(FIBRE_TRANSMIT, OUTPUT);
  fibreOptic.begin(74880);
  Serial.begin(115200);
  SPI.begin();
  SPI.beginTransaction(SPISettings(8000000, MSBFIRST, SPI_MODE3));
  //handle_calibration();
  set_range(range);
  calibrate_adc(1); // forces recalibration, updates time
  flash_led();

  //Use Timer1 for 200Hz interrupts
  cli();                    // Stop interrupts
  TCCR1A = 0;               // Set entire TCCR1A register to 0
  TCCR1B = 0;               // Same for TCCR1B
  TCNT1  = 0;               // Initialize counter value to 0
  OCR1A = (8000000 / ADC_samplefreq) - 1;              // = (8*10^6) / (1000*1) - 1
  TCCR1B |= (1 << WGM12);   // Turn on CTC mode
  TCCR1B |= (1 << CS10);    // Set CS10 bit for x1 prescaler
  TIMSK1 |= (1 << OCIE1A);  // Enable timer compare interrupt
  sei();                    // Allow interrupts
}

ISR(TIMER1_COMPA_vect)
{
  t1_flag = 1;
}

void loop() {
  uint16_t adc_value = read_adc();
  if ((adc_value > 64000) and (last_adc_value < 10000))
  {
    adc_value = 0;
  }
  if ((adc_value < 1500) and (last_adc_value > 55353))
  {
    adc_value = 65535;
  }
  adc_tally += adc_value;
  adc_readings += 1;
  last_adc_value = adc_value;
  
  if (t1_flag == 1) // ~1/ADC_samplefreq has passed
  {
    t1_flag = 0;
    uint16_t adc_average = adc_tally / adc_readings;
    large_tally += adc_average;
    // Send the data in binary format for efficiency. Receiver will interpret gaps.
    uint8_t data[3] = {range, (uint8_t)(adc_average >> 8), (uint8_t)(adc_average & 0xFF)};
    fibreOptic.write(data, 3);
    adc_tally = 0;
    adc_readings = 0;
    i += 1;
  }

  if (i >= 100)
  {
    check_range(large_tally / 100);
    //fibreOptic.print(range);
    large_tally = 0;
    i = 0;
  }
}

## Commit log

2023-07-04 adding files
2023-07-04 Added pictures
